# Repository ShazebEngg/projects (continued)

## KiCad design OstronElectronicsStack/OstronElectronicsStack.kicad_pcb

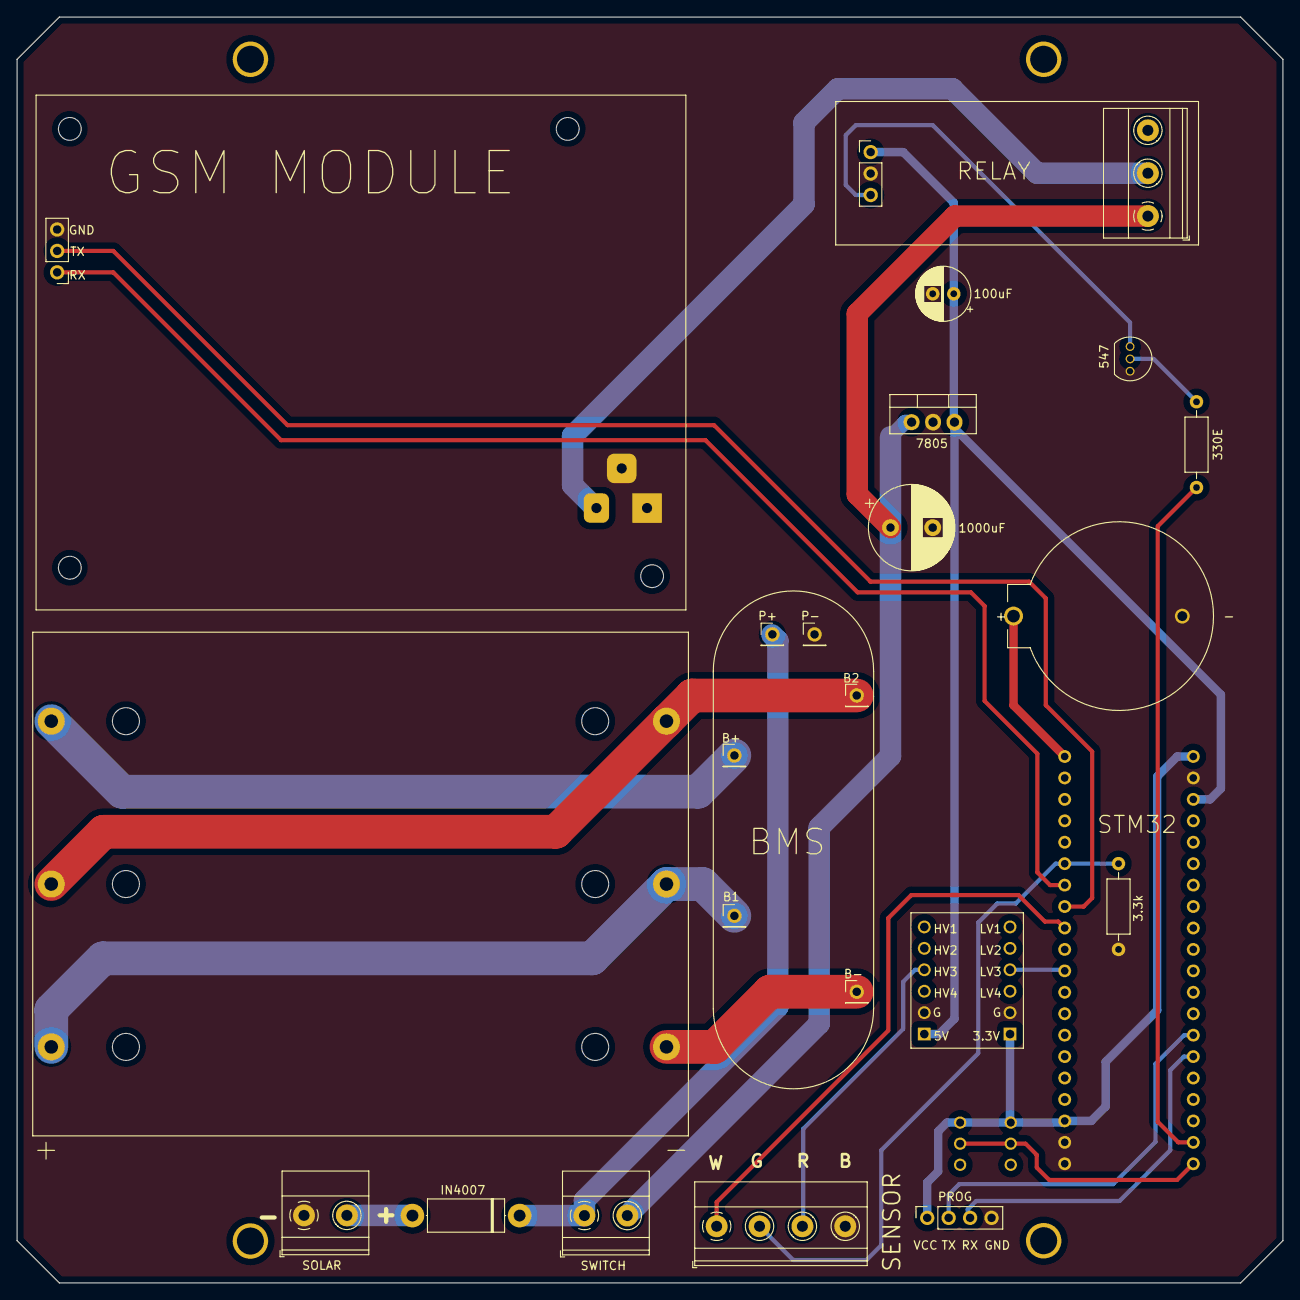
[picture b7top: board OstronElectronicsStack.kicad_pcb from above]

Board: 2 copper layers, 150.0 x 150.0 mm, 26 parts (0 on the bottom side), 24 nets.

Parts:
BT1: BS-7-BLUE; BAT_BS-7-BLUE
BT2: BK-18650-PC6; BAT_BK-18650-PC6
C1: 1000u; CP_Radial_D10.0mm_P5.00mm
C2: 100u; CP_Radial_D6.3mm_P2.50mm
D1: D; D_5W_P12.70mm_Horizontal
J1: GSMSERIAL; PinHeader_1x03_P2.54mm_Vertical
J2: Barrel_Jack_Switch; BarrelJack_Horizontal
J3: P+; PinHeader_1x01_P2.54mm_Vertical
J4: P-; PinHeader_1x01_P2.54mm_Vertical
J5: B+; PinHeader_1x01_P2.54mm_Vertical
J6: B2; PinHeader_1x01_P2.54mm_Vertical
J7: B1; PinHeader_1x01_P2.54mm_Vertical
J8: B-; PinHeader_1x01_P2.54mm_Vertical
J9: SENSOR; TerminalBlock_Phoenix_MKDS-1,5-4-5.08_1x04_P5.08mm_Horizont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
J10: PROG; PinSocket_1x04_P2.54mm_Vertical
J11: SOLAR; TerminalBlock_Phoenix_MKDS-1,5-2-5.08_1x02_P5.08mm_Horizont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
J12: RELAYgsm; TerminalBlock_Phoenix_MKDS-1,5-3-5.08_1x03_P5.08mm_Horizont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
J13: RELAY; PinHeader_1x03_P2.54mm_Vertical
J14: SWITCH; TerminalBlock_Phoenix_MKDS-1,5-2-5.08_1x02_P5.08mm_Horizont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
Q1: BC547; TO-92_Inline
R1: 3.3k; R_Axial_DIN0207_L6.3mm_D2.5mm_P10.16mm_Horizontal
R2: 330; R_Axial_DIN0207_L6.3mm_D2.5mm_P10.16mm_Horizontal
U1: L7805; TO-220-3_Vertical
U2: BOB-12009; CONV_BOB-12009
U3: BP; blue_pill
U4: Y17P21221FP; SW_PVA2EEH21.7NV2

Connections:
+3V3: J10.1, U2.LV, U3.3V3, U4.1, U4.1'
+5V: C2.1, J13.1, U1.3, U2.HV, U3.5V
+12V: D1.1, J3.1, J14.1
+BATT: BT1.+, U3.VBAT
GND: BT1.-, C1.2, C2.2, J1.3, J2.1, J2.3, J4.1, J9.4, J10.4, J11.1, J13.2, Q1.3, R1.2, U1.2, U2.GND_1, U2.GND_2, U3.G
Green: J9.2, R1.1, U3.PA1
unnamed: BT2.1+, J5.1
unnamed: BT2.1-, BT2.2+, J6.1
unnamed: BT2.2-, BT2.3+, J7.1
unnamed: BT2.3-, J8.1
unnamed: D1.2, J11.2
unnamed: J9.3, U2.HV3
unnamed: J10.2, U3.PA10
unnamed: J10.3, U3.PA9
unnamed: J13.3, Q1.1
unnamed: Q1.2, R2.1
unnamed: R2.2, U3.PB13
unnamed: U2.LV3, U3.PA6
unnamed: U3.PB12, U4.0, U4.0'
POWERGSM: J2.2, J12.2
RX: J1.1, U3.PA2
TX: J1.2, U3.PA3
VCC: C1.1, J12.1, J14.2, U1.1
white: J9.1, U3.PA4

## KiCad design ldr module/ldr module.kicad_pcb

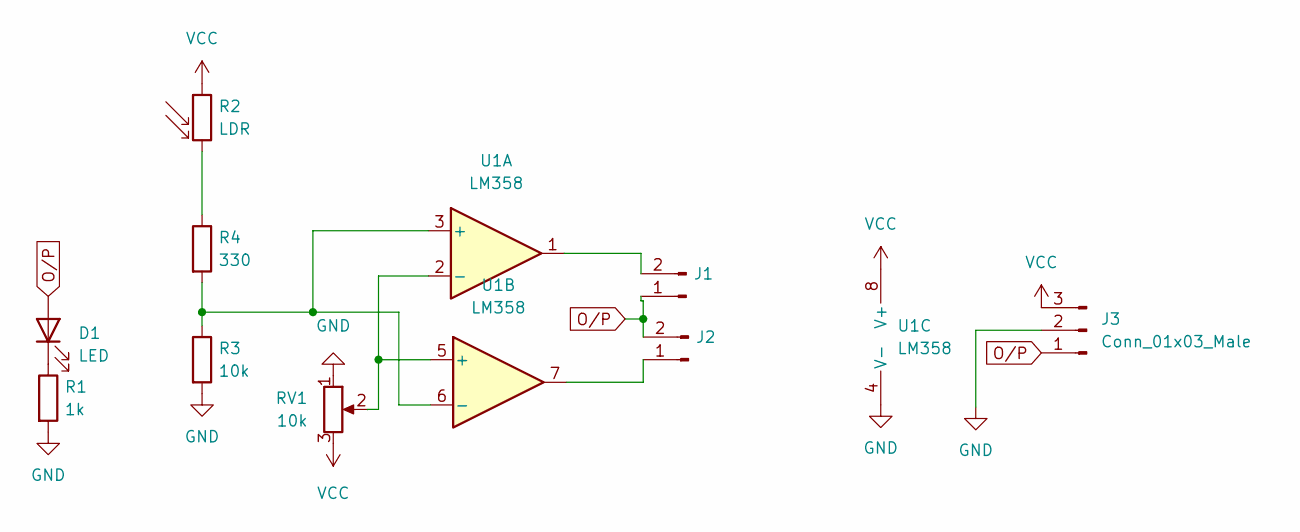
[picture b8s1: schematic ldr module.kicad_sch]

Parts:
D1: LED; LED_D3.0mm
J1, J2: Conn_01x02_Male; PinHeader_1x02_P2.54mm_Vertical
J3: Conn_01x03_Male; PinHeader_1x03_P2.54mm_Vertical
R1: 1k; R_Axial_DIN0309_L9.0mm_D3.2mm_P12.70mm_Horizontal
R2: LDR; R_LDR_4.9x4.2mm_P2.54mm_Vertical
R3: 10k; R_Axial_DIN0309_L9.0mm_D3.2mm_P12.70mm_Horizontal
R4: 330; R_Axial_DIN0309_L9.0mm_D3.2mm_P12.70mm_Horizontal
RV1: 10k; Potentiometer_Runtron_RM-065_Vertical
U1: LM358; DIP-8_W7.62mm

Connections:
GND: J3.2, R1.2, R3.2, RV1.1, U1.4 (V-)
unnamed: D1.1 (K), R1.1
unnamed: J1.2, U1.1
unnamed: J2.1, U1.7
unnamed: R2.2, R4.1
unnamed: R3.1, R4.2, U1.3 (+), U1.6 (-)
unnamed: RV1.2, U1.2 (-), U1.5 (+)
O/P: D1.2 (A), J1.1, J2.2, J3.1
VCC: J3.3, R2.1, RV1.3, U1.8 (V+)

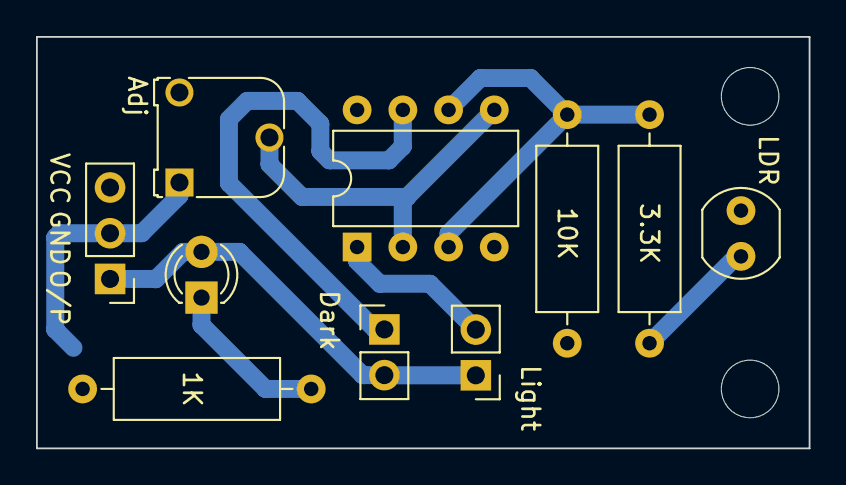
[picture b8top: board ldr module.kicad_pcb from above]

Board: 2 copper layers, 42.9 x 22.9 mm, 10 parts (0 on the bottom side), 9 nets.

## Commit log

2022-10-03 test
    not gate
2022-10-03 ostron scratch
    ic based
2022-10-03 board reset
2022-10-03 ldr/shazeb
2022-10-03 time
2022-10-03 L293D
2022-10-04 laptop
2022-10-04 desktop
2022-10-15 desk
2022-10-28 rasp
2022-10-28 rasp
    added old
